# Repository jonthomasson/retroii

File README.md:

# retroii
Retro ][ is a 6502 based computer based off of the Apple ][. 

Growing up in the 80's I was part of an amazing and special time for computers. Every school I remember had a computer lab loaded with Apple ]['s running such iconic games as Oregon Trail, Odell Lake, and Number Munchers. My mom was a school teacher and somehow we were lucky enough to actually buy an Apple ][ to use at home. That to me sparked an interest in computers and technology that has followed me all these many decades later. 

Towards the beginning of 2019 David Murray, best known as The 8 Bit Guy, posted a video where he described his dream computer. In his video David tells about his childhood, growing up with a VIC 20 computer, and how he missed the closeness to the hardware that those early 8 bit computers provided. David's video got me thinking, and made me ask the tough life question, "what was my dream computer growing up, and what would that look like today?". That question would eventually give way to a year long project I called RETRO ][. The name Retro ][ came as a result of it being inspired and compatible with the original Apple ][, but also because it is a descendant of my first 6502 computer I built in 2015 which was called Retro 1. Retro 1 was similar to the Apple 1, with basically a terminal window to type in BASIC programs. With Retro ][ I wanted to add graphics. I used the Parallax Propeller for video generation in Retro 1, and I knew it could handle the task of more video processing. This is why I'm using it again in Retro ][.

Some basic design decisions for the project. I wanted it to feel like an 80's era computer, with the big beefy through hole components. I wanted it to be simple to understand and easy to program. I wanted it to be made from off the shelf parts that are still being produced today. I wanted it to have at least VGA output so that it could be connected to modern monitors. And for storage I wanted to be able to use a simple SD card. At its core, I wanted this project to be about learning. I wanted something that could give my kids the same sort of experience I had with the Apple ][ so long ago. The simplicity of being able to flip a bit at a ram location and see it result in drawing a pixel on the screen was eye opening to me as a youngster, and I was hoping to replicate that experience now with my own kids.

To meet my design decisions I needed to make a few changes to the original Apple ][ schematic. There were a number of components that were no longer made, like the keyboard encoder, the quad 558 timer, the RAM chips, etc. In addition the timing circuitry needed to be reworked to accommodate the new video requirements. The Apple ][ timing was tightly coupled with the video signal, the RAM refresh rates, as well as the keyboard multiplexer. I wanted to simplify all of this by feeding a simple 1MHz clock into all the key timing circuits. Later on I programmed the Parallax Propeller to take care of the timing. This enabled me to not only stop or single step the clock, but I could overclock the computer as well. I found that the max rate I could reliably get was around 4MHz. At the heart of Retro ][ is a WDC 65C02. I had to modify the original Apple ][ address decoding scheme a bit in order to get it to work for this project. By using the same address decoding as the original Apple ][ I'm able to run the same programs. I got rid of the DRAM and instead used a single 64K dual port static RAM. By using dual port ram, I can easily share the needed video RAM with the Propeller without having to worry about DMA. 

I have two Parallax Propellers in Retro ][. One is solely responsible for video. It simply reads from the video RAM and outputs a VGA signal. The other Propeller is in charge of routines related to the PS/2 keyboard, SD Card, and clock signals. The two Propeller's communicate with one another over an I2C bus. The Propeller ended up being a great fit for this project due to how it can easily handle many parallel processes at once. Instead of using interrupt routines like traditional microcontrollers, the Propeller has what are called "cogs". These cogs are basically tiny single core processes that can run independently. There's 8 cogs in each Propeller. The ability to handle these parallel processes make the Propeller unique in that it's easily programmed like a traditional microcontroller, but you can take advantage of running things in parallel similar to what an FPGA could do.

For the power supply, I wanted to support the same voltages as the original Apple ][ (+5v, -5v, +12v, -12v) as well as 3.3v to power the Propeller's. I settled on the LM2576. I liked the flexibility that the LM2576 provided. It was able to meet the current demands of the project, and came in an easily solderable through whole version. I did find that there was a large inrush current when first applying power, especially for the +12/-12 supply. I'm going to try and rectify this in the next revision.

The last large part of this project are the peripherals. I wanted it to have the same options for expansion as the original Apple ][. I have 8 expansion slots, compatible with existing Apple ][ cards. In addition there are two DB9 Apple ][ joystick ports, as well as two DB15 Gameports. 

For sound output, there's a built in speaker, as well as a headphone jack and a volume control knob to turn the game sounds down when playing at night or around other people. There's also a cassette out/in jack for loading programs on and saving programs to a device like a cassette, or these days a smart phone etc. 

That's it for now! I'll post more project updates as I have time. If you're interested, please make sure and follow my project here on Hackaday, as well as subscribe to my Youtube feed.

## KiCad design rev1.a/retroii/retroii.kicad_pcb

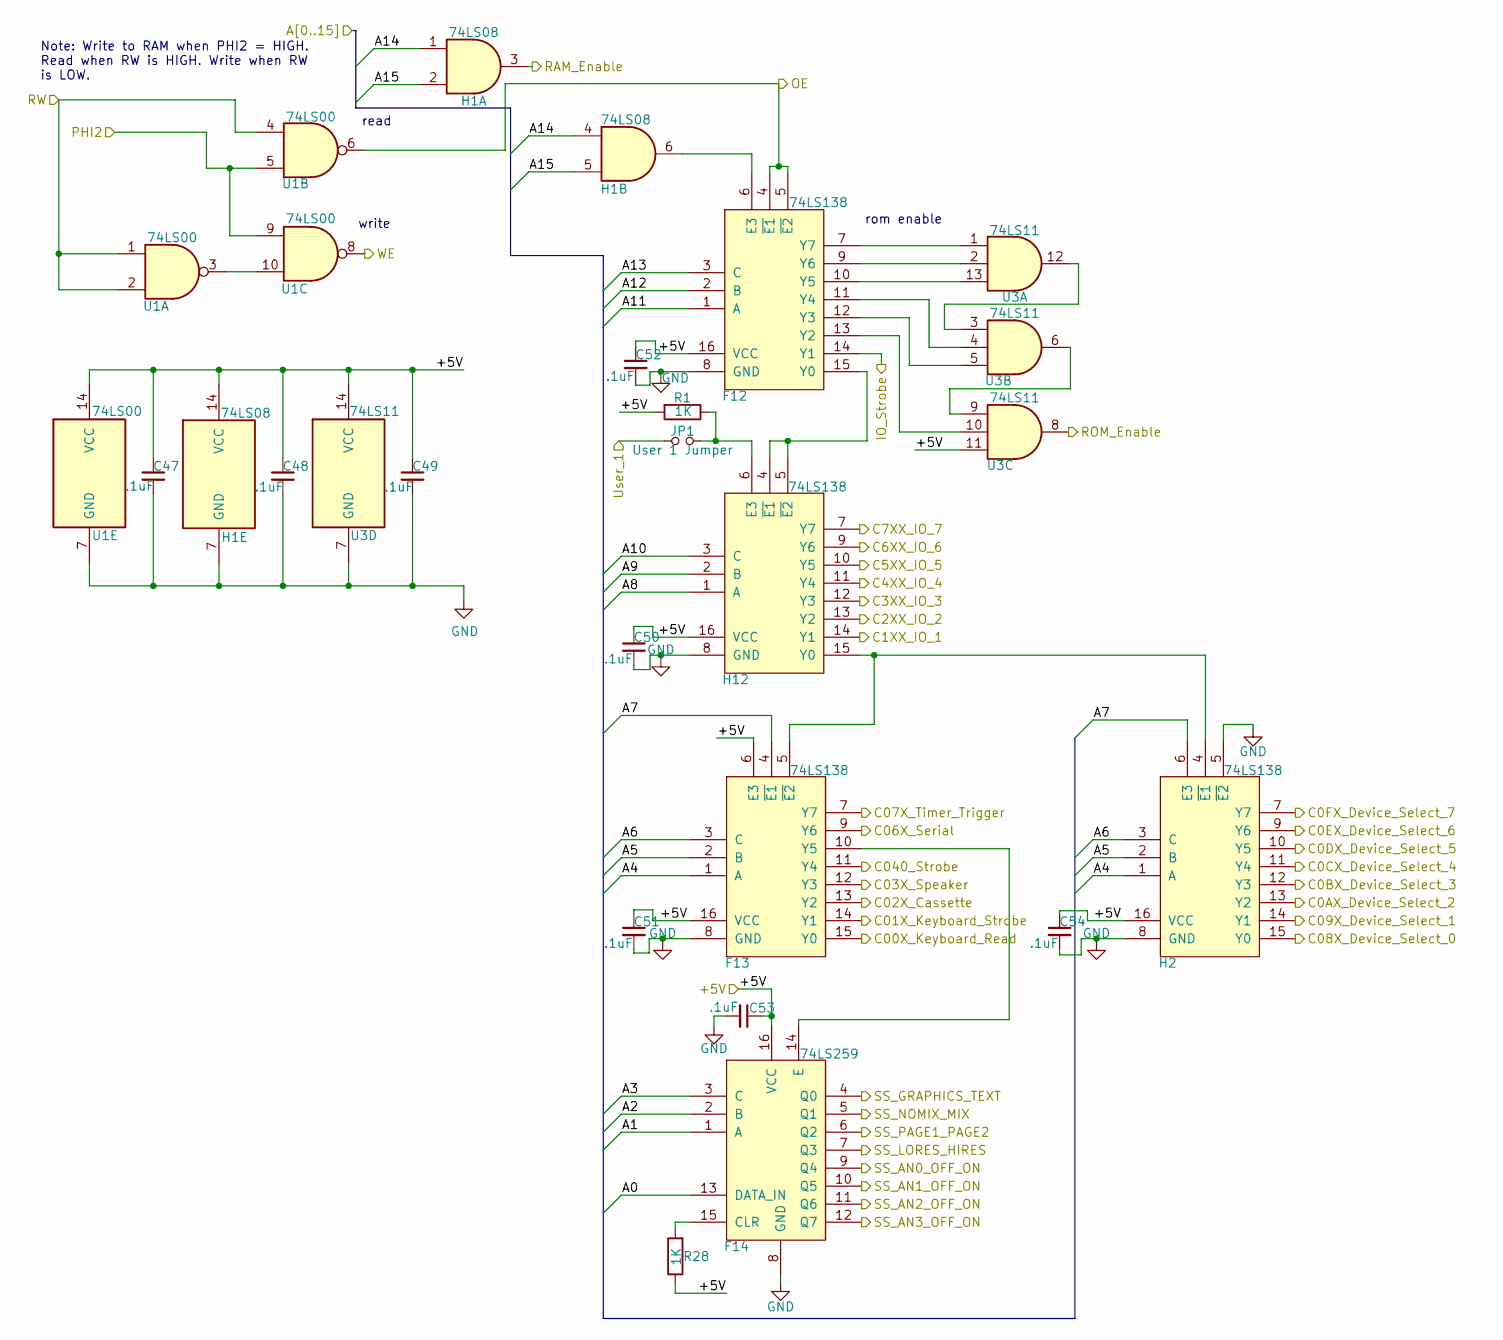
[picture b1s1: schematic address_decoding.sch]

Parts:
C47, C48, C49, C50, C51, C52, C53, C54: .1uF; C_Disc_D3.0mm_W2.0mm_P2.50mm
F12, F13: 74LS138; DIP-16_W7.62mm_Socket_LongPads
F14: 74LS259; DIP-16_W7.62mm_Socket_LongPads
H1: 74LS08; DIP-14_W7.62mm_Socket_LongPads
H2, H12: 74LS138; DIP-16_W7.62mm_Socket_LongPads
JP1: User 1 Jumper; PinHeader_1x02_P2.54mm_Vertical
R1, R28: 1K; R_Axial_DIN0207_L6.3mm_D2.5mm_P10.16mm_Horizontal
U1: 74LS00; DIP-14_W7.62mm_Socket_LongPads
U3: 74LS11; DIP-14_W7.62mm_Socket_LongPads

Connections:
/Address_Decoding/+5V: C47.1, C48.1, C49.1, C50.1, C51.1, C52.1, C53.1, C54.1, F12.16 (VCC), F13.6 (E3), F13.16 (VCC), F14.16 (VCC), H1.14 (VCC), H2.16 (VCC), H12.16 (VCC), R1.2, R28.1, U1.14 (VCC), U3.11, U3.14 (VCC); also elsewhere on the board
/Address_Decoding/A0: F14.13 (DATA_IN); also elsewhere on the board
/Address_Decoding/A1: F14.1 (A); also elsewhere on the board
/Address_Decoding/A2: F14.2 (B); also elsewhere on the board
/Address_Decoding/A3: F14.3 (C); also elsewhere on the board
/Address_Decoding/A4: F13.1 (A), H2.1 (A); also elsewhere on the board
/Address_Decoding/A5: F13.2 (B), H2.2 (B); also elsewhere on the board
/Address_Decoding/A6: F13.3 (C), H2.3 (C); also elsewhere on the board
/Address_Decoding/A7: F13.4 (~E1), H2.6 (E3); also elsewhere on the board
/Address_Decoding/A8: H12.1 (A); also elsewhere on the board
/Address_Decoding/A9: H12.2 (B); also elsewhere on the board
/Address_Decoding/A10: H12.3 (C); also elsewhere on the board
/Address_Decoding/A11: F12.1 (A); also elsewhere on the board
/Address_Decoding/A12: F12.2 (B); also elsewhere on the board
/Address_Decoding/A13: F12.3 (C); also elsewhere on the board
/Address_Decoding/A14: H1.1, H1.4; also elsewhere on the board
/Address_Decoding/A15: H1.2, H1.5; also elsewhere on the board
/Address_Decoding/C0AX_Device_Select_2: H2.13 (Y2); also elsewhere on the board
/Address_Decoding/C0BX_Device_Select_3: H2.12 (Y3); also elsewhere on the board
/Address_Decoding/C0CX_Device_Select_4: H2.11 (Y4); also elsewhere on the board
/Address_Decoding/C0DX_Device_Select_5: H2.10 (Y5); also elsewhere on the board
/Address_Decoding/C0EX_Device_Select_6: H2.9 (Y6); also elsewhere on the board
/Address_Decoding/C0FX_Device_Select_7: H2.7 (Y7); also elsewhere on the board
/Address_Decoding/C00X_Keyboard_Read: F13.15 (Y0); also elsewhere on the board
/Address_Decoding/C1XX_IO_1: H12.14 (Y1); also elsewhere on the board
/Address_Decoding/C01X_Keyboard_Strobe: F13.14 (Y1); also elsewhere on the board
/Address_Decoding/C2XX_IO_2: H12.13 (Y2); also elsewhere on the board
/Address_Decoding/C02X_Cassette: F13.13 (Y2); also elsewhere on the board
/Address_Decoding/C3XX_IO_3: H12.12 (Y3); also elsewhere on the board
/Address_Decoding/C03X_Speaker: F13.12 (Y3); also elsewhere on the board
/Address_Decoding/C4XX_IO_4: H12.11 (Y4); also elsewhere on the board
/Address_Decoding/C5XX_IO_5: H12.10 (Y5); also elsewhere on the board
/Address_Decoding/C6XX_IO_6: H12.9 (Y6); also elsewhere on the board
/Address_Decoding/C06X_Serial: F13.9 (Y6); also elsewhere on the board
/Address_Decoding/C7XX_IO_7: H12.7 (Y7); also elsewhere on the board
/Address_Decoding/C07X_Timer_Trigger: F13.7 (Y7); also elsewhere on the board
/Address_Decoding/C08X_Device_Select_0: H2.15 (Y0); also elsewhere on the board
/Address_Decoding/C09X_Device_Select_1: H2.14 (Y1); also elsewhere on the board
/Address_Decoding/C040_Strobe: F13.11 (Y4); also elsewhere on the board
/Address_Decoding/IO_Strobe: F12.14 (Y1); also elsewhere on the board
/Address_Decoding/OE: F12.4 (~E1), F12.5 (~E2), U1.6; also elsewhere on the board
/Address_Decoding/PHI2: U1.5, U1.9; also elsewhere on the board
/Address_Decoding/RAM_Enable: H1.3; also elsewhere on the board
/Address_Decoding/ROM_Enable: U3.8; also elsewhere on the board
/Address_Decoding/RW: U1.1, U1.2, U1.4; also elsewhere on the board
/Address_Decoding/SS_AN0_OFF_ON: F14.9 (Q4); also elsewhere on the board
/Address_Decoding/SS_AN1_OFF_ON: F14.10 (Q5); also elsewhere on the board
/Address_Decoding/SS_AN2_OFF_ON: F14.11 (Q6); also elsewhere on the board
/Address_Decoding/SS_AN3_OFF_ON: F14.12 (Q7); also elsewhere on the board
/Address_Decoding/SS_GRAPHICS_TEXT: F14.4 (Q0); also elsewhere on the board
/Address_Decoding/SS_LORES_HIRES: F14.7 (Q3); also elsewhere on the board
/Address_Decoding/SS_NOMIX_MIX: F14.5 (Q1); also elsewhere on the board
/Address_Decoding/SS_PAGE1_PAGE2: F14.6 (Q2); also elsewhere on the board
/Address_Decoding/User_1: JP1.1; also elsewhere on the board
/Address_Decoding/WE: U1.8; also elsewhere on the board
GND: C47.2, C48.2, C49.2, C50.2, C51.2, C52.2, C53.2, C54.2, F12.8 (GND), F13.8 (GND), F14.8 (GND), H1.7 (GND), H2.5 (~E2), H2.8 (GND), H12.8 (GND), U1.7 (GND), U3.7 (GND); also elsewhere on the board
unnamed: F12.6 (E3), H1.6
unnamed: F12.7 (Y7), U3.1
unnamed: F12.9 (Y6), U3.2
unnamed: F12.10 (Y5), U3.13
unnamed: F12.11 (Y4), U3.4
unnamed: F12.12 (Y3), U3.5
unnamed: F12.13 (Y2), U3.10
unnamed: F12.15 (Y0), H12.4 (~E1), H12.5 (~E2)
unnamed: F13.5 (~E2), H2.4 (~E1), H12.15 (Y0)
unnamed: F13.10 (Y5), F14.14 (E)
unnamed: F14.15 (CLR), R28.2
unnamed: H12.6 (E3), JP1.2, R1.1
unnamed: U1.3, U1.10
unnamed: U3.6, U3.9
unnamed: U3.3, U3.12

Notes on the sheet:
read
write
rom enable
Note: Write to RAM when PHI2 = HIGH. Read when RW is HIGH. Write when RW is LOW.

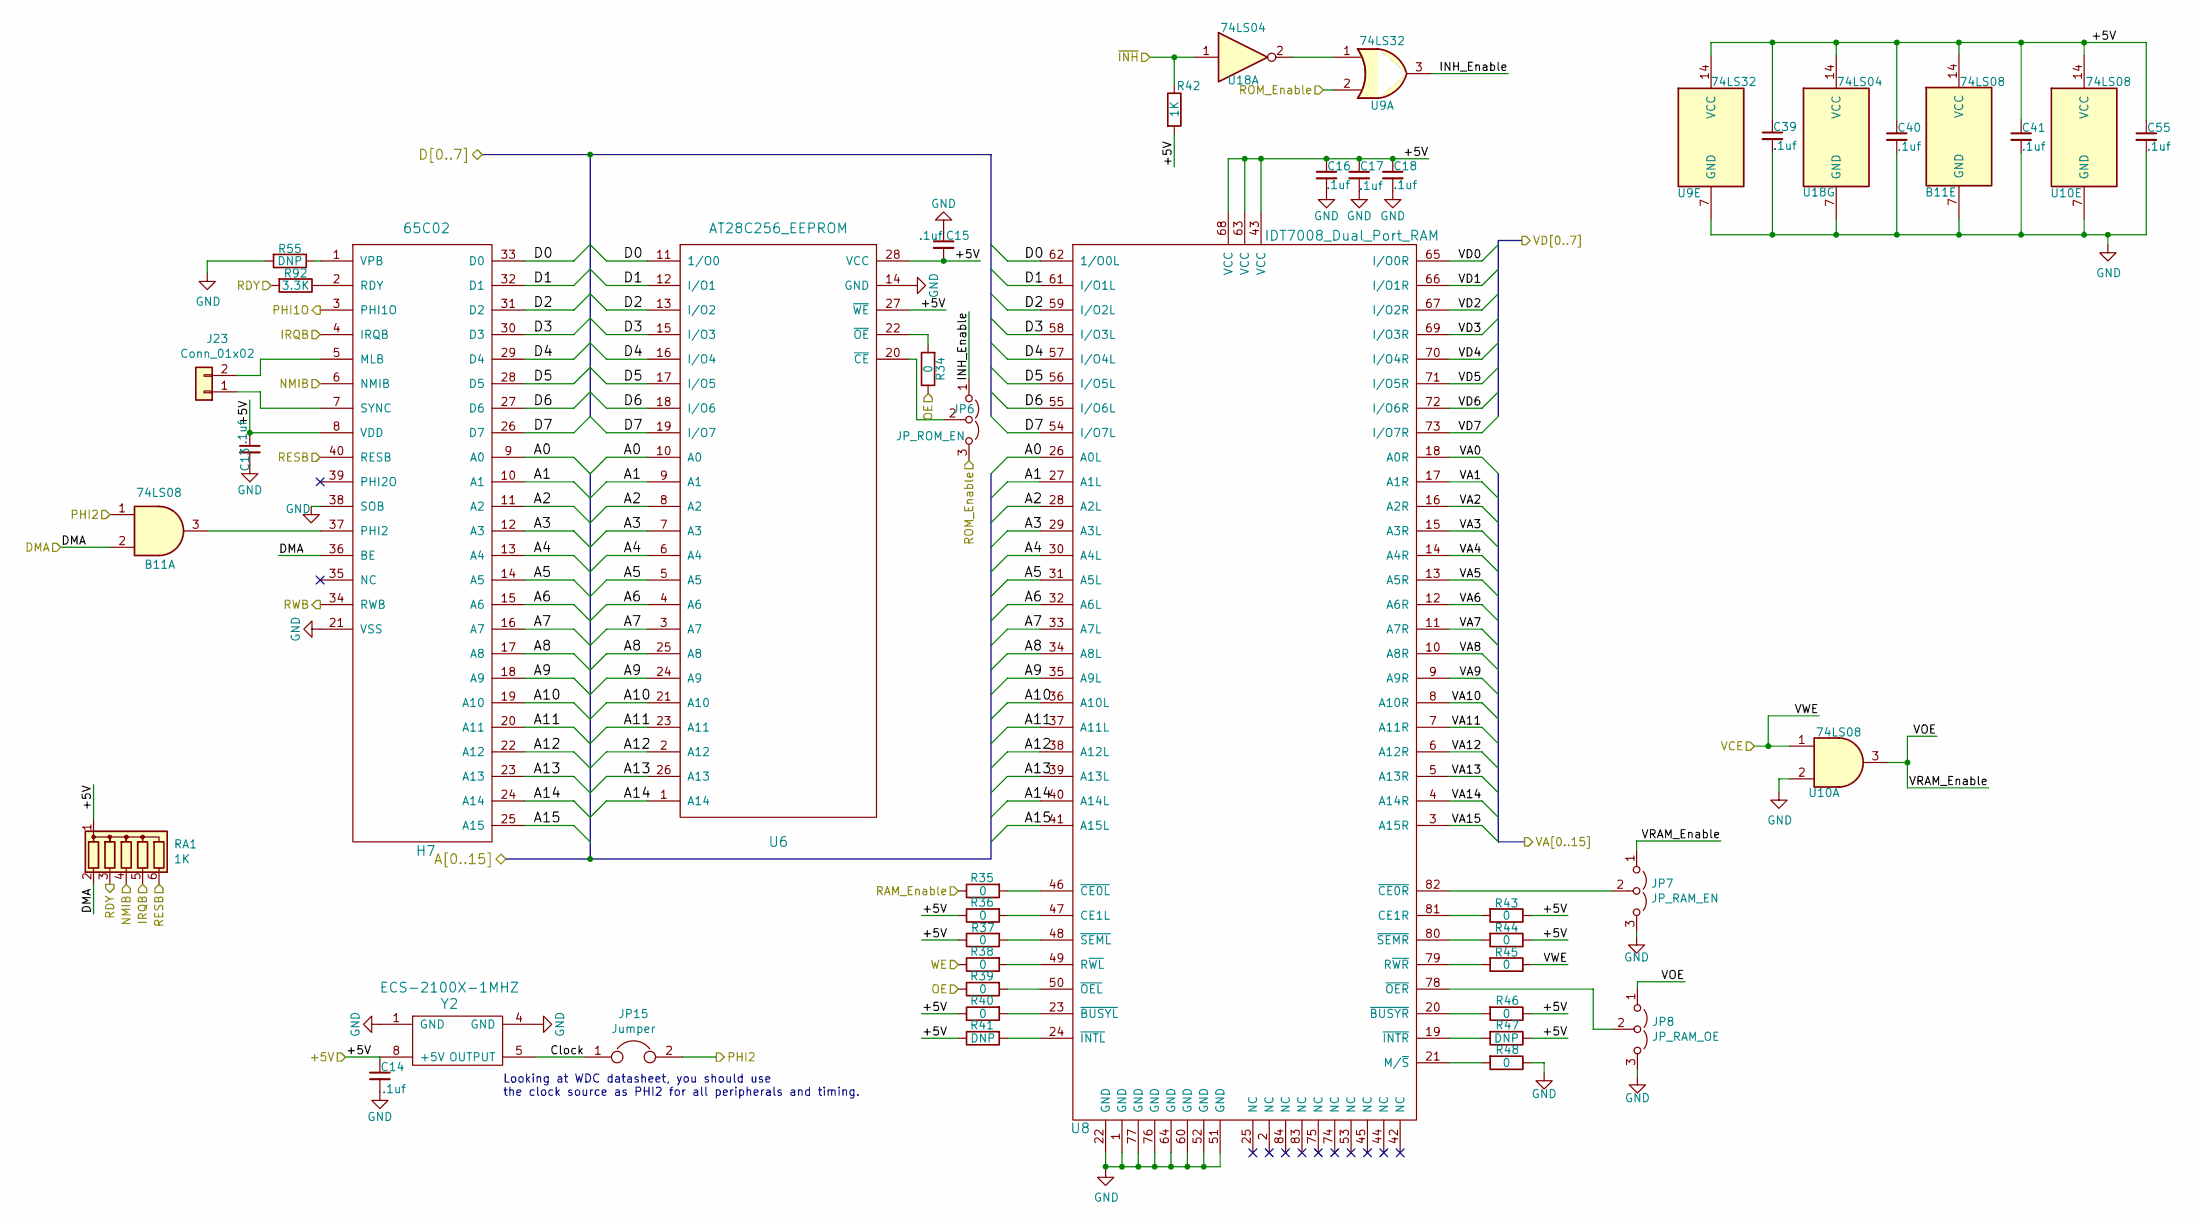
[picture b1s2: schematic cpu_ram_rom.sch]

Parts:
B11: 74LS08; DIP-14_W7.62mm_Socket_LongPads
C13, C14, C15, C16, C17, C18, C39, C40, C41, C55: .1uf; C_Disc_D3.0mm_W2.0mm_P2.50mm
H7: 65C02; DIP-40_W15.24mm_Socket_LongPads
J23: Conn_01x02; PinSocket_1x02_P2.54mm_Vertical
JP6: JP_ROM_EN; PinHeader_1x03_P2.54mm_Vertical
JP7: JP_RAM_EN; PinHeader_1x03_P2.54mm_Vertical
JP8: JP_RAM_OE; PinHeader_1x03_P2.54mm_Vertical
JP15: Jumper; PinHeader_1x02_P2.54mm_Vertical
R34, R35, R36, R37, R38, R39, R40, R43, R44, R45, R46, R48: 0; R_Axial_DIN0207_L6.3mm_D2.5mm_P10.16mm_Horizontal
R41, R47, R55: DNP; R_Axial_DIN0207_L6.3mm_D2.5mm_P10.16mm_Horizontal
R42: 1K; R_Axial_DIN0207_L6.3mm_D2.5mm_P10.16mm_Horizontal
R92: 3.3K; R_Axial_DIN0207_L6.3mm_D2.5mm_P10.16mm_Horizontal
RA1: 1K; R_Array_SIP6
U6: AT28C256_EEPROM; 28-526-11-SOCKET
U8: IDT7008_Dual_Port_RAM; Assman_PLCC84_ACCS084GT
U9: 74LS32; DIP-14_W7.62mm_Socket_LongPads
U10: 74LS08; DIP-14_W7.62mm_Socket_LongPads
U18: 74LS04; DIP-14_W7.62mm_Socket_LongPads
Y2: ECS-2100X-1MHZ; ECS-2100AX

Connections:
/Address_Decoding/+5V: B11.14 (VCC), C13.1, C14.1, C15.2, C16.1, C17.1, C18.1, C39.1, C40.1, C41.1, C55.1, H7.8 (VDD), R36.1, R37.1, R40.1, R41.1, R42.2, R43.1, R44.1, R46.1, R47.1, RA1.1 (common), U6.27 (~WE), U6.28 (VCC), U8.43 (VCC), U8.63 (VCC), U8.68 (VCC), U9.14 (VCC), U10.14 (VCC), U18.14 (VCC), Y2.8 (+5V); also elsewhere on the board
/Address_Decoding/A0: H7.9 (A0), U6.10 (A0), U8.26 (A0L); also elsewhere on the board
/Address_Decoding/A1: H7.10 (A1), U6.9 (A1), U8.27 (A1L); also elsewhere on the board
/Address_Decoding/A2: H7.11 (A2), U6.8 (A2), U8.28 (A2L); also elsewhere on the board
/Address_Decoding/A3: H7.12 (A3), U6.7 (A3), U8.29 (A3L); also elsewhere on the board
/Address_Decoding/A4: H7.13 (A4), U6.6 (A4), U8.30 (A4L); also elsewhere on the board
/Address_Decoding/A5: H7.14 (A5), U6.5 (A5), U8.31 (A5L); also elsewhere on the board
/Address_Decoding/A6: H7.15 (A6), U6.4 (A6), U8.32 (A6L); also elsewhere on the board
/Address_Decoding/A7: H7.16 (A7), U6.3 (A7), U8.33 (A7L); also elsewhere on the board
/Address_Decoding/A8: H7.17 (A8), U6.25 (A8), U8.34 (A8L); also elsewhere on the board
/Address_Decoding/A9: H7.18 (A9), U6.24 (A9), U8.35 (A9L); also elsewhere on the board
/Address_Decoding/A10: H7.19 (A10), U6.21 (A10), U8.36 (A10L); also elsewhere on the board
/Address_Decoding/A11: H7.20 (A11), U6.23 (A11), U8.37 (A11L); also elsewhere on the board
/Address_Decoding/A12: H7.22 (A12), U6.2 (A12), U8.38 (A12L); also elsewhere on the board
/Address_Decoding/A13: H7.23 (A13), U6.26 (A13), U8.39 (A13L); also elsewhere on the board
/Address_Decoding/A14: H7.24 (A14), U6.1 (A14), U8.40 (A14L); also elsewhere on the board
/Address_Decoding/A15: H7.25 (A15), U8.41 (A15L); also elsewhere on the board
/Address_Decoding/OE: R34.1, R39.1; also elsewhere on the board
/Address_Decoding/PHI2: B11.1, JP15.2; also elsewhere on the board
/Address_Decoding/RAM_Enable: R35.1; also elsewhere on the board
/Address_Decoding/ROM_Enable: JP6.3 (B), U9.2; also elsewhere on the board
/Address_Decoding/RW: H7.34 (RWB); also elsewhere on the board
/Address_Decoding/WE: R38.1; also elsewhere on the board
/CPU_RAM_ROM/Clock: JP15.1, Y2.5 (OUTPUT)
/CPU_RAM_ROM/D0: H7.33 (D0), U6.11 (1/O0), U8.62 (1/O0L); also elsewhere on the board
/CPU_RAM_ROM/D1: H7.32 (D1), U6.12 (I/O1), U8.61 (I/O1L); also elsewhere on the board
/CPU_RAM_ROM/D2: H7.31 (D2), U6.13 (I/O2), U8.59 (I/O2L); also elsewhere on the board
/CPU_RAM_ROM/D3: H7.30 (D3), U6.15 (I/O3), U8.58 (I/O3L); also elsewhere on the board
/CPU_RAM_ROM/D4: H7.29 (D4), U6.16 (I/O4), U8.57 (I/O4L); also elsewhere on the board
/CPU_RAM_ROM/D5: H7.28 (D5), U6.17 (I/O5), U8.56 (I/O5L); also elsewhere on the board
/CPU_RAM_ROM/D6: H7.27 (D6), U6.18 (I/O6), U8.55 (I/O6L); also elsewhere on the board
/CPU_RAM_ROM/DMA: B11.2, H7.36 (BE), RA1.2 (R1); also elsewhere on the board
/CPU_RAM_ROM/INH_Enable: JP6.1 (A), U9.3
/CPU_RAM_ROM/IRQB: H7.4 (IRQB), RA1.5 (R4); also elsewhere on the board
/CPU_RAM_ROM/NMIB: H7.6 (NMIB), RA1.4 (R3); also elsewhere on the board
/CPU_RAM_ROM/PHI1O: H7.3 (PHI1O); also elsewhere on the board
/CPU_RAM_ROM/RDY: R92.2, RA1.3 (R2); also elsewhere on the board
/CPU_RAM_ROM/RESB: H7.40 (RESB), RA1.6 (R5); also elsewhere on the board
/CPU_RAM_ROM/VA0: U8.18 (A0R); also elsewhere on the board
/CPU_RAM_ROM/VA1: U8.17 (A1R); also elsewhere on the board
/CPU_RAM_ROM/VA2: U8.16 (A2R); also elsewhere on the board
/CPU_RAM_ROM/VA3: U8.15 (A3R); also elsewhere on the board
/CPU_RAM_ROM/VA4: U8.14 (A4R); also elsewhere on the board
/CPU_RAM_ROM/VA5: U8.13 (A5R); also elsewhere on the board
/CPU_RAM_ROM/VA6: U8.12 (A6R); also elsewhere on the board
/CPU_RAM_ROM/VA7: U8.11 (A7R); also elsewhere on the board
/CPU_RAM_ROM/VA8: U8.10 (A8R); also elsewhere on the board
/CPU_RAM_ROM/VA9: U8.9 (A9R); also elsewhere on the board
/CPU_RAM_ROM/VA10: U8.8 (A10R); also elsewhere on the board
/CPU_RAM_ROM/VA11: U8.7 (A11R); also elsewhere on the board
/CPU_RAM_ROM/VA12: U8.6 (A12R); also elsewhere on the board
/CPU_RAM_ROM/VA13: U8.5 (A13R); also elsewhere on the board
/CPU_RAM_ROM/VA14: U8.4 (A14R); also elsewhere on the board
/CPU_RAM_ROM/VA15: U8.3 (A15R); also elsewhere on the board
/CPU_RAM_ROM/VCE: R45.1, U10.1; also elsewhere on the board
/CPU_RAM_ROM/VD0: U8.65 (I/O0R); also elsewhere on the board
/CPU_RAM_ROM/VD1: U8.66 (I/O1R); also elsewhere on the board
/CPU_RAM_ROM/VD2: U8.67 (I/O2R); also elsewhere on the board
/CPU_RAM_ROM/VD3: U8.69 (I/O3R); also elsewhere on the board
/CPU_RAM_ROM/VD4: U8.70 (I/O4R); also elsewhere on the board
/CPU_RAM_ROM/VD5: U8.71 (I/O5R); also elsewhere on the board
/CPU_RAM_ROM/VD6: U8.72 (I/O6R); also elsewhere on the board
/CPU_RAM_ROM/VD7: U8.73 (I/O7R); also elsewhere on the board
/CPU_RAM_ROM/VOE: JP7.1 (A), JP8.1 (A), U10.3
/CPU_RAM_ROM/~INH: R42.1, U18.1; also elsewhere on the board
GND: B11.7 (GND), C13.2, C14.2, C15.1, C16.2, C17.2, C18.2, C39.2, C40.2, C41.2, C55.2, H7.21 (VSS), H7.38 (SOB), JP7.3 (B), JP8.3 (B), R48.1, R55.2, U6.14 (GND), U8.1 (GND), U8.22 (GND), U8.51 (GND), U8.52 (GND), U8.60 (GND), U8.64 (GND), U8.76 (GND), U8.77 (GND), U9.7 (GND), U10.2, U10.7 (GND), U18.7 (GND), Y2.1 (GND), Y2.4 (GND); also elsewhere on the board
unnamed: B11.3, H7.37 (PHI2)
unnamed: H7.1 (VPB), R55.1
unnamed: H7.2 (RDY), R92.1
unnamed: H7.5 (MLB), J23.2
unnamed: H7.7 (SYNC), J23.1
unnamed: JP6.2 (C), U6.20 (~CE)
unnamed: JP7.2 (C), U8.82 (~CE0R)
unnamed: JP8.2 (C), U8.78 (~OER)
unnamed: R34.2, U6.22 (~OE)
unnamed: R35.2, U8.46 (~CE0L)
unnamed: R36.2, U8.47 (CE1L)
unnamed: R37.2, U8.48 (~SEML)
unnamed: R38.2, U8.49 (R~WL)
unnamed: R39.2, U8.50 (~OEL)
unnamed: R40.2, U8.23 (~BUSYL)
unnamed: R41.2, U8.24 (~INTL)
unnamed: R43.2, U8.81 (CE1R)
unnamed: R44.2, U8.80 (~SEMR)
unnamed: R45.2, U8.79 (R~WR)
unnamed: R46.2, U8.20 (~BUSYR)
unnamed: R47.2, U8.19 (~INTR)
unnamed: R48.2, U8.21 (M/~S)
unnamed: U9.1, U18.2

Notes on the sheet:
Looking at WDC datasheet, you should use the clock source as PHI2 for all peripherals and timing.

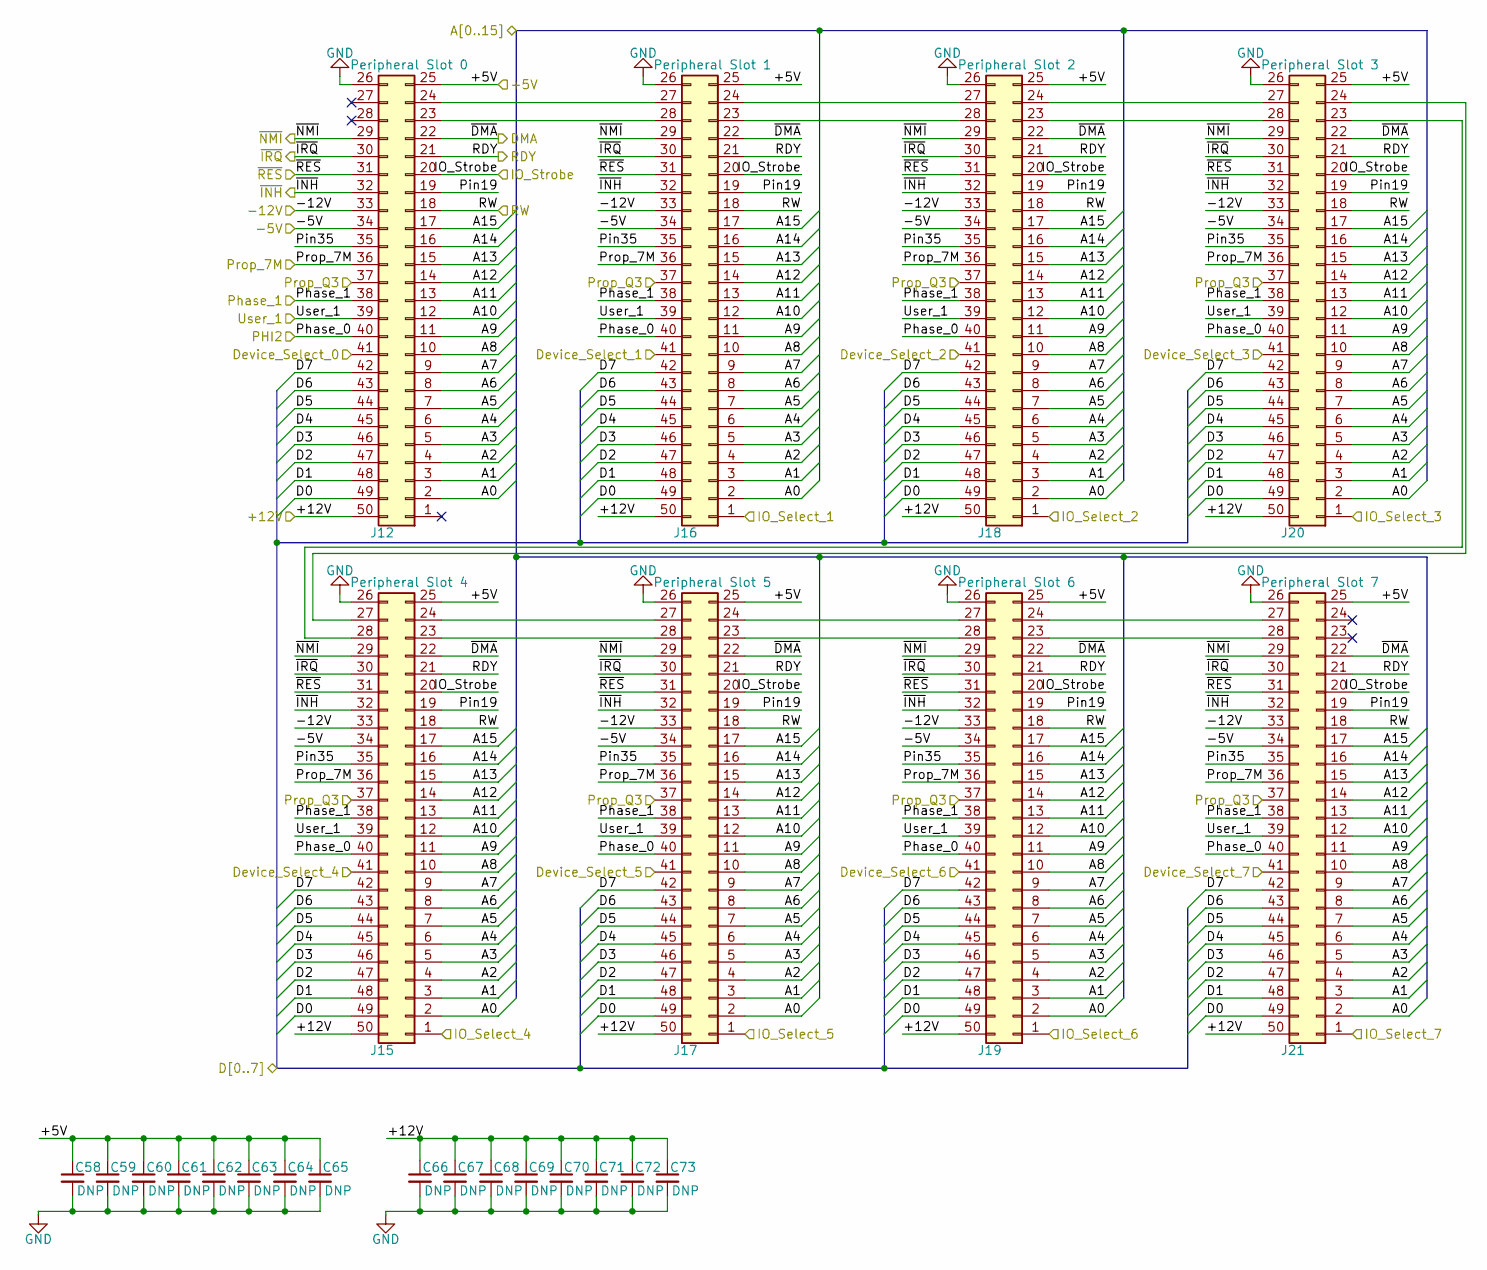
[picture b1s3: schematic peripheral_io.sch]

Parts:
C58, C59, C60, C61, C62, C63, C64, C65, C66, C67, C68, C69, C70, C71, C72, C73: DNP; C_Disc_D3.0mm_W2.0mm_P2.50mm
J12: Peripheral Slot 0; TE_5530841-5
J15: Peripheral Slot 4; TE_5530841-5
J16: Peripheral Slot 1; TE_5530841-5
J17: Peripheral Slot 5; TE_5530841-5
J18: Peripheral Slot 2; TE_5530841-5
J19: Peripheral Slot 6; TE_5530841-5
J20: Peripheral Slot 3; TE_5530841-5
J21: Peripheral Slot 7; TE_5530841-5

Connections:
/Address_Decoding/+5V: C58.1, C59.1, C60.1, C61.1, C62.1, C63.1, C64.1, C65.1, J12.25, J15.25, J16.25, J17.25, J18.25, J19.25, J20.25, J21.25; also elsewhere on the board
/Address_Decoding/A0: J12.2, J15.2, J16.2, J17.2, J18.2, J19.2, J20.2, J21.2; also elsewhere on the board
/Address_Decoding/A1: J12.3, J15.3, J16.3, J17.3, J18.3, J19.3, J20.3, J21.3; also elsewhere on the board
/Address_Decoding/A2: J12.4, J15.4, J16.4, J17.4, J18.4, J19.4, J20.4, J21.4; also elsewhere on the board
/Address_Decoding/A3: J12.5, J15.5, J16.5, J17.5, J18.5, J19.5, J20.5, J21.5; also elsewhere on the board
/Address_Decoding/A4: J12.6, J15.6, J16.6, J17.6, J18.6, J19.6, J20.6, J21.6; also elsewhere on the board
/Address_Decoding/A5: J12.7, J15.7, J16.7, J17.7, J18.7, J19.7, J20.7, J21.7; also elsewhere on the board
/Address_Decoding/A6: J12.8, J15.8, J16.8, J17.8, J18.8, J19.8, J20.8, J21.8; also elsewhere on the board
/Address_Decoding/A8: J12.10, J15.10, J16.10, J17.10, J18.10, J19.10, J20.10, J21.10; also elsewhere on the board
/Address_Decoding/A9: J12.11, J15.11, J16.11, J17.11, J18.11, J19.11, J20.11, J21.11; also elsewhere on the board
/Address_Decoding/A10: J12.12, J15.12, J16.12, J17.12, J18.12, J19.12, J20.12, J21.12; also elsewhere on the board
/Address_Decoding/A11: J12.13, J15.13, J16.13, J17.13, J18.13, J19.13, J20.13, J21.13; also elsewhere on the board
/Address_Decoding/A12: J12.14, J15.14, J16.14, J17.14, J18.14, J19.14, J20.14, J21.14; also elsewhere on the board
/Address_Decoding/A13: J12.15, J15.15, J16.15, J17.15, J18.15, J19.15, J20.15, J21.15; also elsewhere on the board
/Address_Decoding/A14: J12.16, J15.16, J16.16, J17.16, J18.16, J19.16, J20.16, J21.16; also elsewhere on the board
/Address_Decoding/A15: J12.17, J15.17, J16.17, J17.17, J18.17, J19.17, J20.17, J21.17; also elsewhere on the board
/Address_Decoding/C0AX_Device_Select_2: J18.41; also elsewhere on the board
/Address_Decoding/C0BX_Device_Select_3: J20.41; also elsewhere on the board
/Address_Decoding/C0CX_Device_Select_4: J15.41; also elsewhere on the board
/Address_Decoding/C0DX_Device_Select_5: J17.41; also elsewhere on the board
/Address_Decoding/C0EX_Device_Select_6: J19.41; also elsewhere on the board
/Address_Decoding/C0FX_Device_Select_7: J21.41; also elsewhere on the board
/Address_Decoding/C1XX_IO_1: J16.1; also elsewhere on the board
/Address_Decoding/C2XX_IO_2: J18.1; also elsewhere on the board
/Address_Decoding/C3XX_IO_3: J20.1; also elsewhere on the board
/Address_Decoding/C4XX_IO_4: J15.1; also elsewhere on the board
/Address_Decoding/C5XX_IO_5: J17.1; also elsewhere on the board
/Address_Decoding/C6XX_IO_6: J19.1; also elsewhere on the board
/Address_Decoding/C7XX_IO_7: J21.1; also elsewhere on the board
/Address_Decoding/C08X_Device_Select_0: J12.41; also elsewhere on the board
/Address_Decoding/C09X_Device_Select_1: J16.41; also elsewhere on the board
/Address_Decoding/IO_Strobe: J12.20, J15.20, J16.20, J17.20, J18.20, J19.20, J20.20, J21.20; also elsewhere on the board
/Address_Decoding/PHI2: J12.40, J15.40, J16.40, J17.40, J18.40, J19.40, J20.40, J21.40; also elsewhere on the board
/Address_Decoding/RW: J12.18, J15.18, J16.18, J17.18, J18.18, J19.18, J20.18, J21.18; also elsewhere on the board
/Address_Decoding/User_1: J12.39, J15.39, J16.39, J17.39, J18.39, J19.39, J20.39, J21.39; also elsewhere on the board
/CPU_RAM_ROM/D0: J12.49, J15.49, J16.49, J17.49, J18.49, J19.49, J20.49, J21.49; also elsewhere on the board
/CPU_RAM_ROM/D1: J12.48, J15.48, J16.48, J17.48, J18.48, J19.48, J20.48, J21.48; also elsewhere on the board
/CPU_RAM_ROM/D2: J12.47, J15.47, J16.47, J17.47, J18.47, J19.47, J20.47, J21.47; also elsewhere on the board
/CPU_RAM_ROM/D3: J12.46, J15.46, J16.46, J17.46, J18.46, J19.46, J20.46, J21.46; also elsewhere on the board
/CPU_RAM_ROM/D4: J12.45, J15.45, J16.45, J17.45, J18.45, J19.45, J20.45, J21.45; also elsewhere on the board
/CPU_RAM_ROM/D5: J12.44, J15.44, J16.44, J17.44, J18.44, J19.44, J20.44, J21.44; also elsewhere on the board
/CPU_RAM_ROM/D6: J12.43, J15.43, J16.43, J17.43, J18.43, J19.43, J20.43, J21.43; also elsewhere on the board
/CPU_RAM_ROM/DMA: J12.22, J15.22, J16.22, J17.22, J18.22, J19.22, J20.22, J21.22; also elsewhere on the board
/CPU_RAM_ROM/IRQB: J12.30, J15.30, J16.30, J17.30, J18.30, J19.30, J20.30, J21.30; also elsewhere on the board
/CPU_RAM_ROM/NMIB: J12.29, J15.29, J16.29, J17.29, J18.29, J19.29, J20.29, J21.29; also elsewhere on the board
/CPU_RAM_ROM/PHI1O: J12.38, J15.38, J16.38, J17.38, J18.38, J19.38, J20.38, J21.38; also elsewhere on the board
/CPU_RAM_ROM/RDY: J12.21, J15.21, J16.21, J17.21, J18.21, J19.21, J20.21, J21.21; also elsewhere on the board
/CPU_RAM_ROM/RESB: J12.31, J15.31, J16.31, J17.31, J18.31, J19.31, J20.31, J21.31; also elsewhere on the board
/CPU_RAM_ROM/~INH: J12.32, J15.32, J16.32, J17.32, J18.32, J19.32, J20.32, J21.32; also elsewhere on the board
/Peripheral_IO/+12V: C66.1, C67.1, C68.1, C69.1, C70.1, C71.1, C72.1, C73.1, J12.50, J15.50, J16.50, J17.50, J18.50, J19.50, J20.50, J21.50; also elsewhere on the board
/Peripheral_IO/-5V: J12.34, J15.34, J16.34, J17.34, J18.34, J19.34, J20.34, J21.34; also elsewhere on the board
/Peripheral_IO/-12V: J12.33, J15.33, J16.33, J17.33, J18.33, J19.33, J20.33, J21.33; also elsewhere on the board
/Peripheral_IO/Pin19: J12.19, J15.19, J16.19, J17.19, J18.19, J19.19, J20.19, J21.19
/Peripheral_IO/Pin35: J12.35, J15.35, J16.35, J17.35, J18.35, J19.35, J20.35, J21.35
/Peripheral_IO/Prop_7M: J12.36, J15.36, J16.36, J17.36, J18.36, J19.36, J20.36, J21.36; also elsewhere on the board
/Peripheral_IO/Prop_Q3: J12.37, J15.37, J16.37, J17.37, J18.37, J19.37, J20.37, J21.37; also elsewhere on the board
GND: C58.2, C59.2, C60.2, C61.2, C62.2, C63.2, C64.2, C65.2, C66.2, C67.2, C68.2, C69.2, C70.2, C71.2, C72.2, C73.2, J12.26, J15.26, J16.26, J17.26, J18.26, J19.26, J20.26, J21.26; also elsewhere on the board
unnamed: J12.23, J16.28
unnamed: J12.24, J16.27
unnamed: J15.23, J17.28
unnamed: J15.24, J17.27
unnamed: J15.27, J20.24
unnamed: J15.28, J20.23
unnamed: J16.23, J18.28
unnamed: J16.24, J18.27
unnamed: J17.23, J19.28
unnamed: J17.24, J19.27
unnamed: J18.23, J20.28
unnamed: J18.24, J20.27
unnamed: J19.23, J21.28
unnamed: J19.24, J21.27
